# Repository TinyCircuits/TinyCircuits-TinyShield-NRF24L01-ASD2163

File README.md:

# TinyCircuits TinyShield NRF24L01+ Radio Board
# ASD2613 Rev3

These are the design files for the TinyCircuits ASD2163 Rev3 PCB.  This is a TinyShield board that has a Nordic Semiconductor NRF24L01+ 2.4GHZ  chipset, local power supply and level shifters to connect between the TinyDuino and the radio transceiver. 

Format is in Cadsoft Eagle format - Eagle version 6.2 was used for the original design.

For more infomation on this, check out the product page at TinyCircuits.com:  https://tinycircuits.com/products/nrf24-2-4ghz-radio-tinyshieldc.html

# License:

Design by TinyCircuits.
All design files are released under the Creative Commons Attribution Share-Alike 3.0 License, see the following link for details: http://creativecommons.org/licenses/by-sa/3.0

All text above must be included in any redistribution or derived design

This project uses designs and concepts developed as part of the Arduino project and the LilyPad project.  The TinyCircuits design files themselves (schematics, PCB and libraries) are not directly derived from these works' design files and have been created new, however the concepts and basic architecture behind the TinyDuino and TinyLily products are derived and we thank the hard work of the organizations below for their contributions to open-source hardware:
  
Original Arduino Uno Design by Team Arduino

LilyPad Arduino Design by Leah Buechley and Sparkfun Electronics

Please support the open-source hardware community

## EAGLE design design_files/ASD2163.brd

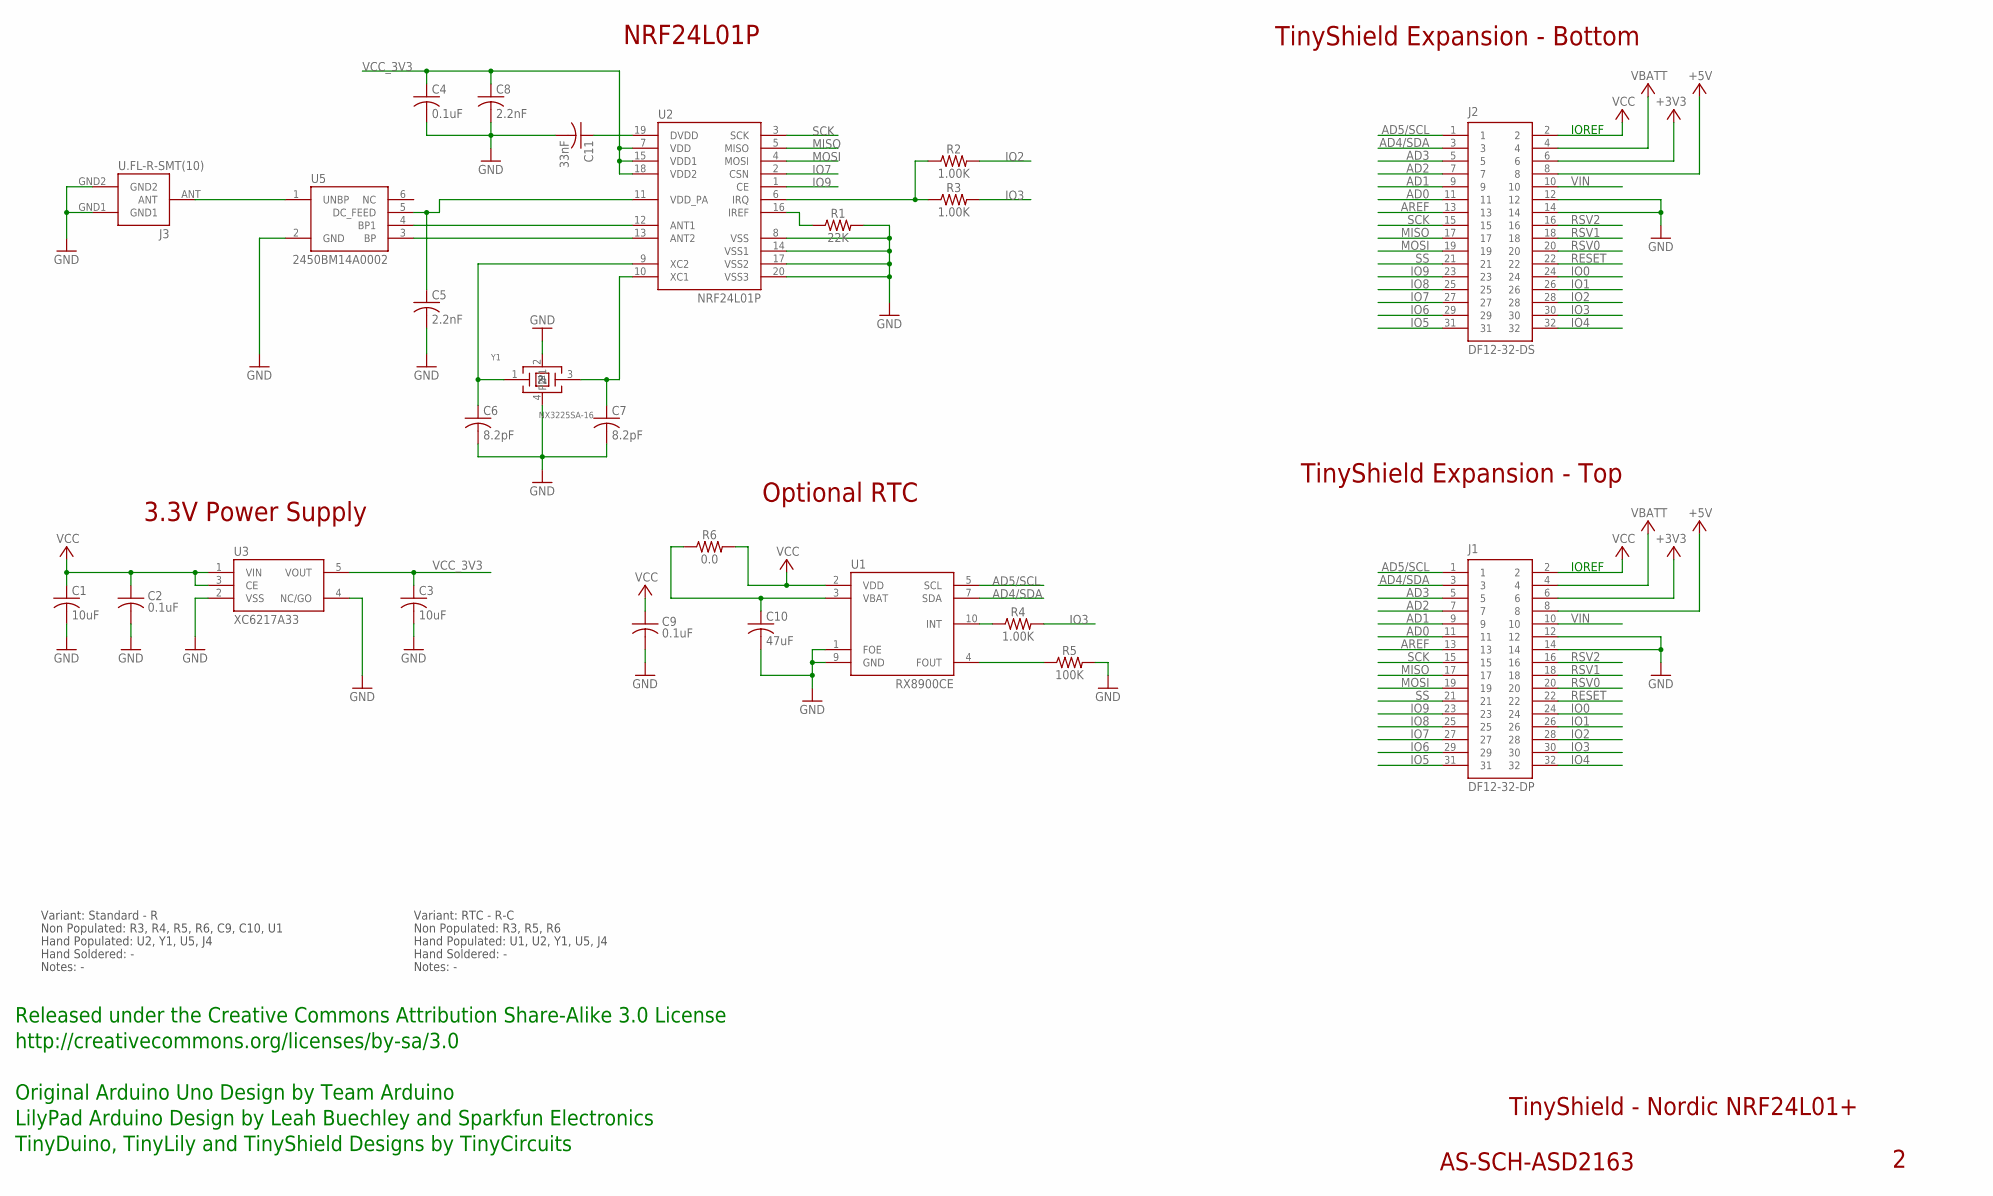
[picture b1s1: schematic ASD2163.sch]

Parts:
C1, C3: 10uF; C0603; PARTNO AS-ITM-00002
C2, C4, C9: 0.1uF; C0402; PARTNO AS-ITM-00008
C5: 2.2nF; C0402
C6, C7: 8.2pF; C0402; PARTNO AS-ITM-00247
C8: 2.2nF; C0402; PARTNO AS-ITM-00085
C10: 47uF; C1206
C11: 33nF; C0402; PARTNO AS-ITM-00248
J1: DF12-32-DP; PARTNO AS-ITM-00015
J2: DF12-32-DS; PARTNO AS-ITM-00012
J3: U.FL-R-SMT(10)
R1: 22K; 0402
R2, R3, R4: 1.00K; 0402; PARTNO AS-ITM-00003
R5: 100K; 0402
R6: 0.0; 0402; PARTNO AS-ITM-00076
U1: RX8900CE
U2: NRF24L01P; QFN20-NO_PAD
U3: XC6217A33; SOT-25; PARTNO AS-ITM-00249
U5: 2450BM14A0002
Y1: NX3225SA-16; ABM11; PARTNO AS-ITM-00228

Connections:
+3V3: J1.6, J2.6
+5V: J1.8, J2.8
AD0: J1.11, J2.11
AD1: J1.9, J2.9
AD2: J1.7, J2.7
AD3: J1.5, J2.5
AD4/SDA: J1.3, J2.3, U1.7 (SDA)
AD5/SCL: J1.1, J2.1, U1.5 (SCL)
AREF: J1.13, J2.13
GND: C1.2, C2.2, C3.2, C4.2, C5.2, C6.2, C7.2, C8.2, C9.2, C10.2, C11.2, J1.12, J1.14, J2.12, J2.14, J3.GND1, J3.GND2, R1.2, R5.2, U1.1 (FOE), U1.9 (GND), U2.8 (VSS), U2.14 (VSS1), U2.17 (VSS2), U2.20 (VSS3), U3.2 (VSS), U3.4 (NC/GO), U5.2 (GND), Y1.2, Y1.4 (P1)
IO0: J1.24, J2.24
IO1: J1.26, J2.26
IO2: J1.28, J2.28, R2.2
IO3: J1.30, J2.30, R3.2, R4.2
IO4: J1.32, J2.32
IO5: J1.31, J2.31
IO6: J1.29, J2.29
IO7: J1.27, J2.27, U2.2 (CSN)
IO8: J1.25, J2.25
IO9: J1.23, J2.23, U2.1 (CE)
MISO: J1.17, J2.17, U2.5 (MISO)
MOSI: J1.19, J2.19, U2.4 (MOSI)
unnamed: R1.1, U2.16 (IREF)
unnamed: C6.1, U2.9 (XC2), Y1.1
unnamed: J3.ANT, U5.1 (UNBP)
unnamed: C10.1, R6.1, U1.3 (VBAT)
unnamed: C11.1, U2.19 (DVDD)
unnamed: U2.13 (ANT2), U5.3 (BP)
unnamed: U2.12 (ANT1), U5.4 (BP1)
unnamed: C5.1, U2.11 (VDD_PA), U5.5 (DC_FEED)
unnamed: C7.1, U2.10 (XC1), Y1.3 (2)
unnamed: R5.1, U1.4 (FOUT)
RDYN: R2.1, R3.1, U2.6 (IRQ)
RDYN1: R4.1, U1.10 (INT)
RESET: J1.22, J2.22
RSV0: J1.20, J2.20
RSV1: J1.18, J2.18
RSV2: J1.16, J2.16
SCK: J1.15, J2.15, U2.3 (SCK)
SS: J1.21, J2.21
VBATT: J1.4, J2.4
VCC: C1.1, C2.1, C9.1, J1.2, J2.2, R6.2, U1.2 (VDD), U3.1 (VIN), U3.3 (CE)
VCC_3V3: C3.1, C4.1, C8.1, U2.7 (VDD), U2.15 (VDD1), U2.18 (VDD2), U3.5 (VOUT)
VIN: J1.10, J2.10

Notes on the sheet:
TinyShield Expansion - Bottom
TinyShield - Nordic NRF24L01+
AS-SCH-ASD2163
TinyShield Expansion - Top
IOREF
Released under the Creative Commons Attribution Share-Alike 3.0 License
http://creativecommons.org/licenses/by-sa/3.0
LilyPad Arduino Design by Leah Buechley and Sparkfun Electronics
TinyDuino, TinyLily and TinyShield Designs by TinyCircuits
Original Arduino Uno Design by Team Arduino
3.3V Power Supply
NRF24L01P
Optional RTC
Non Populated: R3, R4, R5, R6, C9, C10, U1
Hand Populated: U2, Y1, U5, J4
Hand Soldered: -
Notes: -
Variant: Standard - R
Non Populated: R3, R5, R6
Hand Populated: U1, U2, Y1, U5, J4
Variant: RTC - R-C

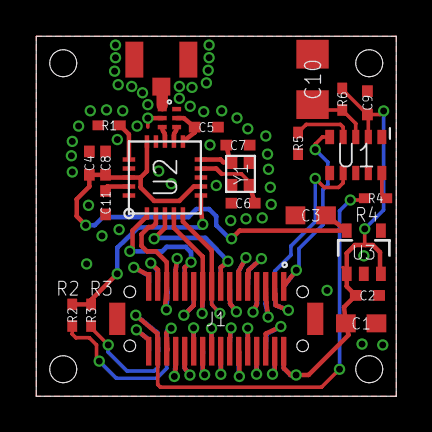
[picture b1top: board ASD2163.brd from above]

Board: 2 copper layers, 20.0 x 20.0 mm, 26 parts (1 on the bottom side), 44 nets.

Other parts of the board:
U$1: DOCFIELD-TINYCIRCUITS-PCB

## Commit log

2019-01-02 update format
2019-01-07 updated comments
2019-05-22 added images and .zip for sketch
2019-05-23 updated images
2019-05-28 added examples and libraries
2019-06-04 updated tutorial images
2019-06-04 added example code
2019-06-04 commented code
2020-02-11 image update
2020-07-28 Add CAD data
2020-08-14 Update CAD drawing
2021-01-11 fix the schematic
